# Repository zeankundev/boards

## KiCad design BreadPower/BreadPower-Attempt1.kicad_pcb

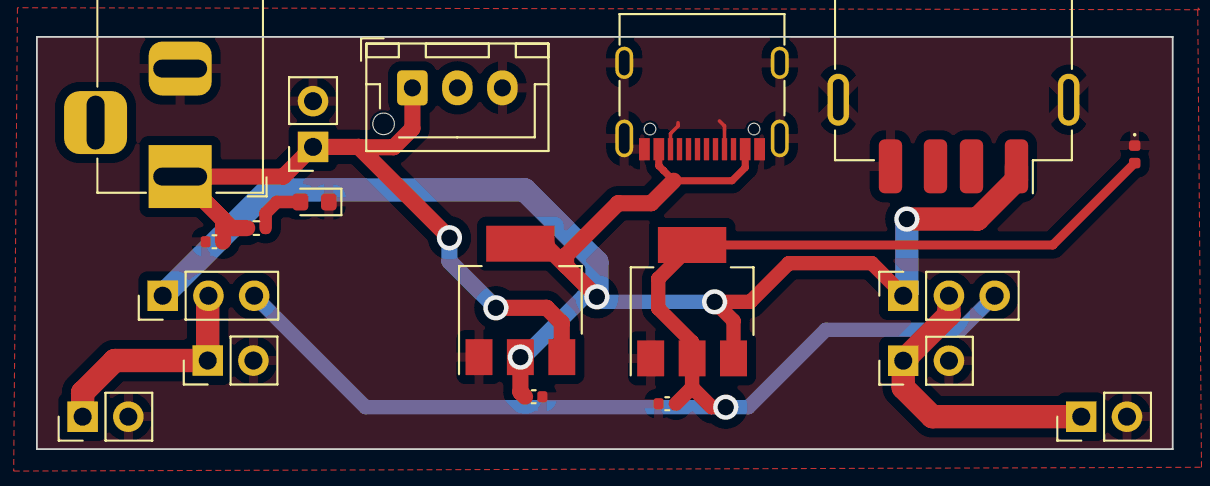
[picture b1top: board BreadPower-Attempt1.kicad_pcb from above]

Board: 2 copper layers, 63.1 x 22.9 mm, 19 parts (0 on the bottom side), 7 nets.

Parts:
C1: 22u; C_0402_1005Metric
C2: 8uF; C_0402_1005Metric
C3: 12uF; C_0402_1005Metric
D1: D; D_0603_1608Metric
D2: GREEN; LED_0402_1005Metric
J1: Barrel_Jack_MountingPin; BarrelJack_Horizontal
J2: USB_C_Receptacle_USB2.0; USB_C_Receptacle_G-Switch_GT-USB-7010ASV
J3: USB_A; USB_A_Receptacle_GCT_USB1046
J4: Conn_01x03_Socket; JST_XH_B3B-XH-AM_1x03_P2.50mm_Vertical
J5: Conn_01x03; PinHeader_1x03_P2.54mm_Vertical
J6: Conn_01x02; PinSocket_1x02_P2.54mm_Vertical
J7: Conn_01x03; PinSocket_1x03_P2.54mm_Vertical
J8, J9, J10, J11: Conn_01x02; PinHeader_1x02_P2.54mm_Vertical
R1: 3; R_0402_1005Metric
U1: AMS1117-5.0; SOT-223-3_TabPin2
U2: AMS1117-3.3; SOT-223-3_TabPin2

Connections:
+3.3V: C3.1, D2.2 (A), J5.3, J7.3, U2.2 (VO)
+5V: C2.1, J2.A4 (VBUS), J2.A9 (VBUS), J2.B4 (VBUS), J2.B9 (VBUS), J3.1 (VBUS), J5.1, J7.1, U1.2 (VO), U2.3 (VI)
/OUTPUT_VDD_1: J5.2, J8.1, J11.1
/OUTPUT_VDD_2: J7.2, J9.1, J10.1
GND: C1.2, C2.2, C3.2, D1.1 (K), D2.1 (K), J1.2, J2.A1 (GND), J2.A5 (CC1), J2.A12 (GND), J2.B1 (GND), J2.B5 (CC2), J2.B12 (GND), J2.S1 (SHIELD), J3.4 (GND), J3.5 (Shield), J4.3, J6.2, J8.2, J9.2, J10.2, J11.2, U1.1 (GND), U2.1 (GND)
unnamed: D1.2 (A), R1.2
VDD: C1.1, J1.1, J4.1, J6.1, R1.1, U1.3 (VI)

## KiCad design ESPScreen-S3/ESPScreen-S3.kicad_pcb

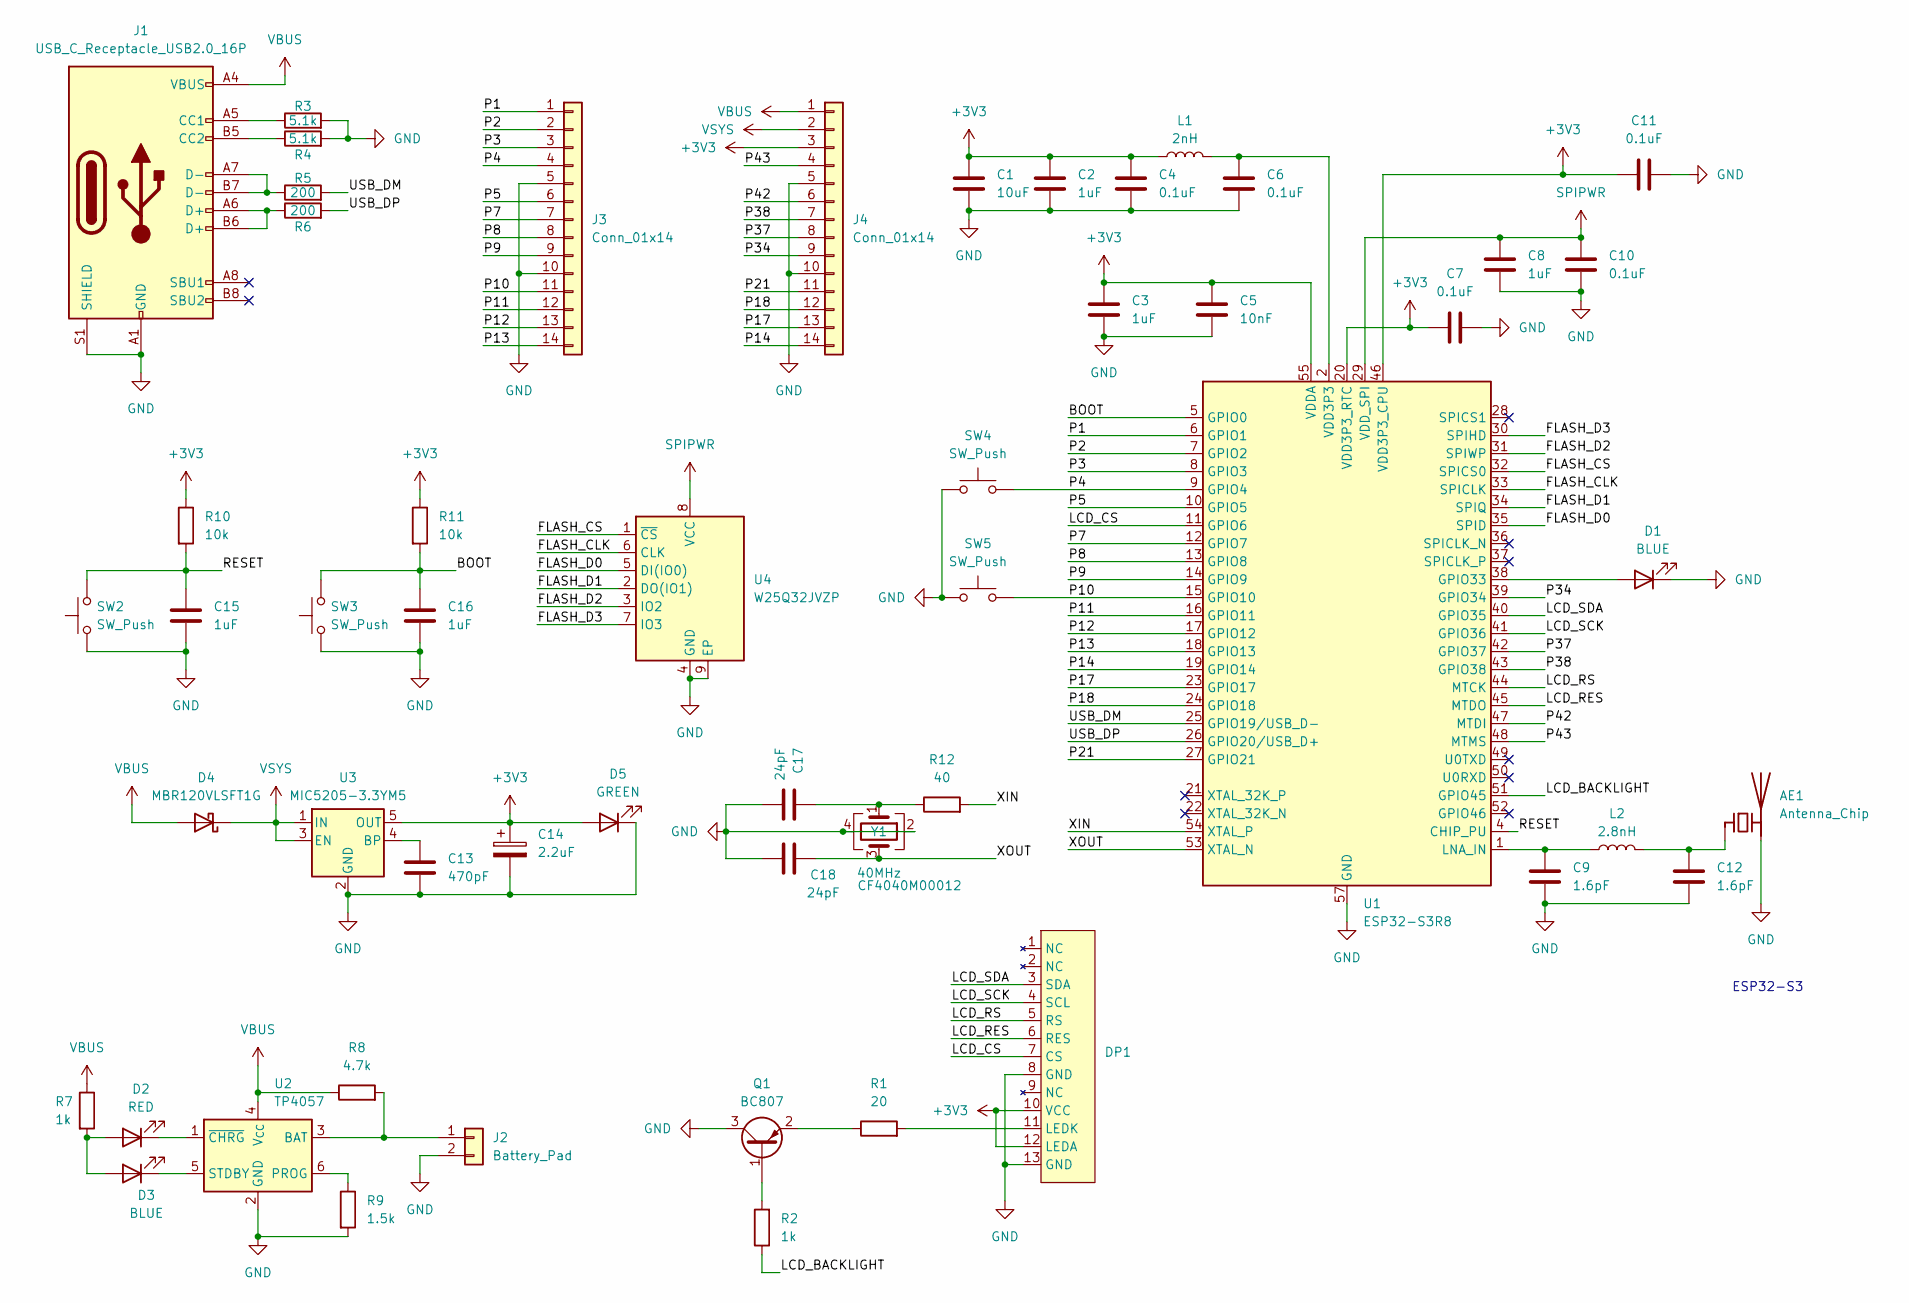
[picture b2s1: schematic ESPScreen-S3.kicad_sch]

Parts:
AE1: Antenna_Chip; Texas_SWRA117D_2.4GHz_Left
C1: 10uF; C_0402_1005Metric
C2, C3, C8, C15, C16: 1uF; C_0402_1005Metric
C4, C6, C7, C10, C11: 0.1uF; C_0402_1005Metric
C5: 10nF; C_0402_1005Metric
C9, C12: 1.6pF; C_0402_1005Metric
C13: 470pF; C_0402_1005Metric
C14: 2.2uF; CP_EIA-1608-08_AVX-J
C17, C18: 24pF; C_0402_1005Metric
D1, D3: BLUE; LED_0402_1005Metric
D2: RED; LED_0402_1005Metric
D4: MBR120VLSFT1G; D_SOD-123F
D5: GREEN; LED_0402_1005Metric
DP1: N114-2413THBIG01-H13
J1: USB_C_Receptacle_USB2.0_16P; USB_C_Receptacle_GCT_USB4105-xx-A_16P_TopMnt_Horizontal
J2: Battery_Pad; SolderWire-0.1sqmm_1x02_P3.6mm_D0.4mm_OD1mm
J3, J4: Conn_01x14; PinHeader_1x14_P2.54mm_Vertical
L1: 2nH; L_0402_1005Metric
L2: 2.8nH; L_0402_1005Metric
Q1: BC807; SOT-23
R1: 20; R_0402_1005Metric
R2, R7: 1k; R_0402_1005Metric
R3, R4: 5.1k; R_0402_1005Metric
R5, R6: 200; R_0402_1005Metric
R8: 4.7k; R_0402_1005Metric
R9: 1.5k; R_0402_1005Metric
R10, R11: 10k; R_0402_1005Metric
R12: 40; R_0402_1005Metric
SW2, SW3: SW_Push; SW_SPST_EVQP7C
SW4, SW5: SW_Push; SW_Push_1P1T_NO_Vertical_Wuerth_434133025816
U1: ESP32-S3R8; QFN-56-1EP_7x7mm_P0.4mm_EP4x4mm
U2: TP4057; TSOT-23-6
U3: MIC5205-3.3YM5; SOT-23-5
U4: W25Q32JVZP; WSON-8-1EP_6x5mm_P1.27mm_EP3.4x4.3mm
Y1: 40MHz; Crystal_SMD_3225-4Pin_3.2x2.5mm

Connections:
+3V3: C1.1, C2.1, C3.1, C4.1, C5.1, C7.1, C11.1, C14.1, D5.2 (A), DP1.10 (VCC), DP1.12 (LEDA), J4.3, L1.1, R10.1, R11.1, U1.20 (VDD3P3_RTC), U1.46 (VDD3P3_CPU), U1.55 (VDDA), U1.56 (VDDA), U3.5 (OUT)
/BOOT: C16.1, R11.2, SW3.2, U1.5 (GPIO0)
/FLASH_CLK: U1.33 (SPICLK), U4.6 (CLK)
/FLASH_CS: U1.32 (SPICS0), U4.1 (~CS)
/FLASH_D0: U1.35 (SPID), U4.5 (DI(IO0))
/FLASH_D1: U1.34 (SPIQ), U4.2 (DO(IO1))
/FLASH_D2: U1.31 (SPIWP), U4.3 (IO2)
/FLASH_D3: U1.30 (SPIHD), U4.7 (IO3)
/LCD_BACKLIGHT: R2.1, U1.51 (GPIO45)
/LCD_CS: DP1.7 (CS), U1.11 (GPIO6)
/LCD_RES: DP1.6 (RES), U1.45 (MTDO)
/LCD_RS: DP1.5 (RS), U1.44 (MTCK)
/LCD_SCK: DP1.4 (SCL), U1.41 (GPIO36)
/LCD_SDA: DP1.3 (SDA), U1.40 (GPIO35)
/P1: J3.1, U1.6 (GPIO1)
/P2: J3.2, U1.7 (GPIO2)
/P3: J3.3, U1.8 (GPIO3)
/P4: J3.4, SW4.2, U1.9 (GPIO4)
/P5: J3.6, U1.10 (GPIO5)
/P7: J3.7, U1.12 (GPIO7)
/P8: J3.8, U1.13 (GPIO8)
/P9: J3.9, U1.14 (GPIO9)
/P10: J3.11, SW5.2, U1.15 (GPIO10)
/P11: J3.12, U1.16 (GPIO11)
/P12: J3.13, U1.17 (GPIO12)
/P13: J3.14, U1.18 (GPIO13)
/P14: J4.14, U1.19 (GPIO14)
/P17: J4.13, U1.23 (GPIO17)
/P18: J4.12, U1.24 (GPIO18)
/P21: J4.11, U1.27 (GPIO21)
/P34: J4.9, U1.39 (GPIO34)
/P37: J4.8, U1.42 (GPIO37)
/P38: J4.7, U1.43 (GPIO38)
/P42: J4.6, U1.47 (MTDI)
/P43: J4.4, U1.48 (MTMS)
/RESET: C15.1, R10.2, SW2.2, U1.4 (CHIP_PU)
/USB_DM: R5.2, U1.25 (GPIO19/USB_D-)
/USB_DP: R6.2, U1.26 (GPIO20/USB_D+)
/XIN: R12.2, U1.54 (XTAL_P)
/XOUT: C18.1, U1.53 (XTAL_N), Y1.3
GND: AE1.2 (PCB_Trace), C1.2, C2.2, C3.2, C4.2, C5.2, C6.2, C7.2, C8.2, C9.2, C10.1, C11.2, C12.2, C13.2, C14.2, C15.2, C16.2, C17.2, C18.2, D1.1 (K), D5.1 (K), DP1.8 (GND), DP1.13 (GND), J1.A1 (GND), J1.A12 (GND), J1.B1 (GND), J1.B12 (GND), J1.S1 (SHIELD), J2.2, J3.5, J3.10, J4.5, J4.10, Q1.3 (C), R3.2, R4.2, R9.2, SW2.1, SW3.1, SW4.1, SW5.1, U1.57 (GND), U2.2 (GND), U3.2 (GND), U4.4 (GND), U4.9 (EP), Y1.2, Y1.4
unnamed: AE1.1 (FEED), C12.1, L2.2
unnamed: C6.1, L1.2, U1.2 (VDD3P3), U1.3 (VDD3P3)
unnamed: C17.1, R12.1, Y1.1
unnamed: D1.2 (A), U1.38 (GPIO33)
unnamed: D2.2 (A), D3.2 (A), R7.2
unnamed: D2.1 (K), U2.1 (~CHRG)
unnamed: D3.1 (K), U2.5 (STDBY)
unnamed: DP1.11 (LEDK), R1.2
unnamed: J1.A5 (CC1), R3.1
unnamed: J1.B5 (CC2), R4.1
unnamed: J1.A6 (D+), J1.B6 (D+), R6.1
unnamed: J1.A7 (D-), J1.B7 (D-), R5.1
unnamed: J2.1, R8.2, U2.3 (BAT)
unnamed: Q1.1 (B), R2.2
unnamed: Q1.2 (E), R1.1
unnamed: C9.1, L2.1, U1.1 (LNA_IN)
unnamed: R9.1, U2.6 (PROG)
unnamed: C13.1, U3.4 (BP)
SPIPWR: C8.1, C10.2, U1.29 (VDD_SPI), U4.8 (VCC)
VBUS: D4.2 (A), J1.A4 (VBUS), J1.A9 (VBUS), J1.B4 (VBUS), J1.B9 (VBUS), J4.1, R7.1, R8.1, U2.4 (V_{CC})
VSYS: D4.1 (K), J4.2, U3.1 (IN), U3.3 (EN)

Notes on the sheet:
ESP32-S3

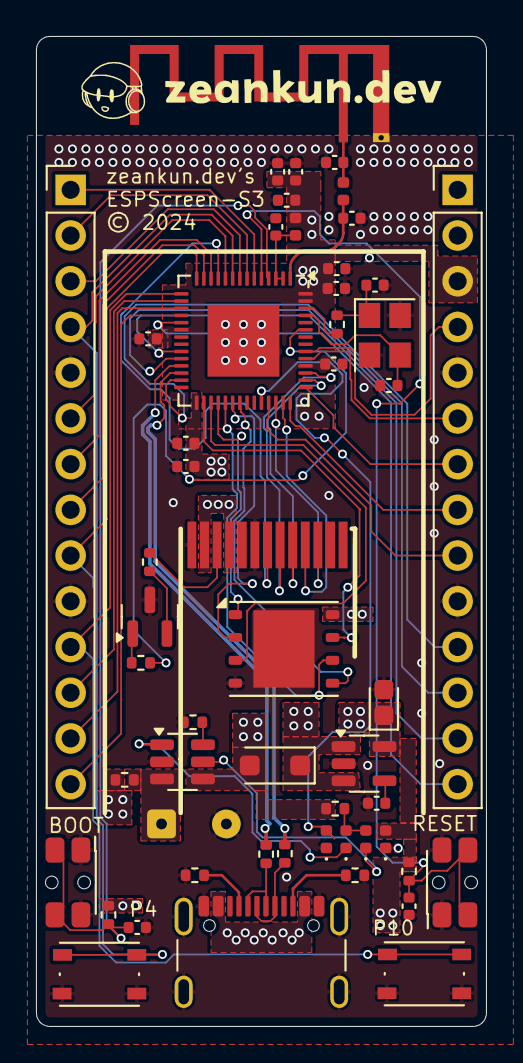
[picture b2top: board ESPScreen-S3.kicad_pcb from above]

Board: 4 copper layers, 25.0 x 55.0 mm, 53 parts (0 on the bottom side), 62 nets.

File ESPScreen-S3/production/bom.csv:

Designator,Footprint,Quantity,Value,LCSC Part #
AE1,Texas_SWRA117D_2.4GHz_Left,1,Antenna_Chip,
C1,0402,1,10uF,
"C10, C11, C4, C6, C7",0402,5,0.1uF,
"C12, C9",0402,2,1.6pF,
C13,0402,1,470pF,
C14,CP_EIA-1608-08_AVX-J,1,2.2uF,
"C15, C16, C2, C3, C8",0402,5,1uF,
"C17, C18",0402,2,24pF,
C5,0402,1,10nF,
"D1, D3",0402,2,BLUE,
D2,0402,1,RED,
D4,D_SOD-123F,1,MBR120VLSFT1G,
D5,0402,1,GREEN,
DP1,N114-2413THBIG01-H13,1,~,
J1,USB_C_Receptacle_GCT_USB4105-xx-A_16P_TopMnt_Horizontal,1,USB_C_Receptacle_USB2.0_16P,
J2,SolderWire-0.1sqmm_1x02_P3.6mm_D0.4mm_OD1mm,1,Battery_Pad,
"J3, J4",PinHeader_1x14_P2.54mm_Vertical,2,Conn_01x14,
L1,0402,1,2nH,
L2,0402,1,2.8nH,
Q1,SOT-23,1,BC807,
R1,0402,1,20,
"R10, R11",0402,2,10k,
R12,0402,1,40,
"R2, R7",0402,2,1k,
"R3, R4",0402,2,5.1k,
"R5, R6",0402,2,200,
R8,0402,1,4.7k,
R9,0402,1,1.5k,
"SW2, SW3",SW_SPST_EVQP7C,2,SW_Push,
"SW4, SW5",SW_Push_1P1T_NO_Vertical_Wuerth_434133025816,2,SW_Push,
U1,QFN-56-1EP_7x7mm_P0.4mm_EP4x4mm,1,ESP32-S3R8,
U2,TSOT-23-6,1,TP4057,
U3,SOT-23-5,1,MIC5205-3.3YM5,
U4,WSON-8-1EP_6x5mm_P1.27mm_EP3.4x4.3mm,1,W25Q32JVZP,
Y1,Crystal_SMD_3225-4Pin_3.2x2.5mm,1,40MHz,

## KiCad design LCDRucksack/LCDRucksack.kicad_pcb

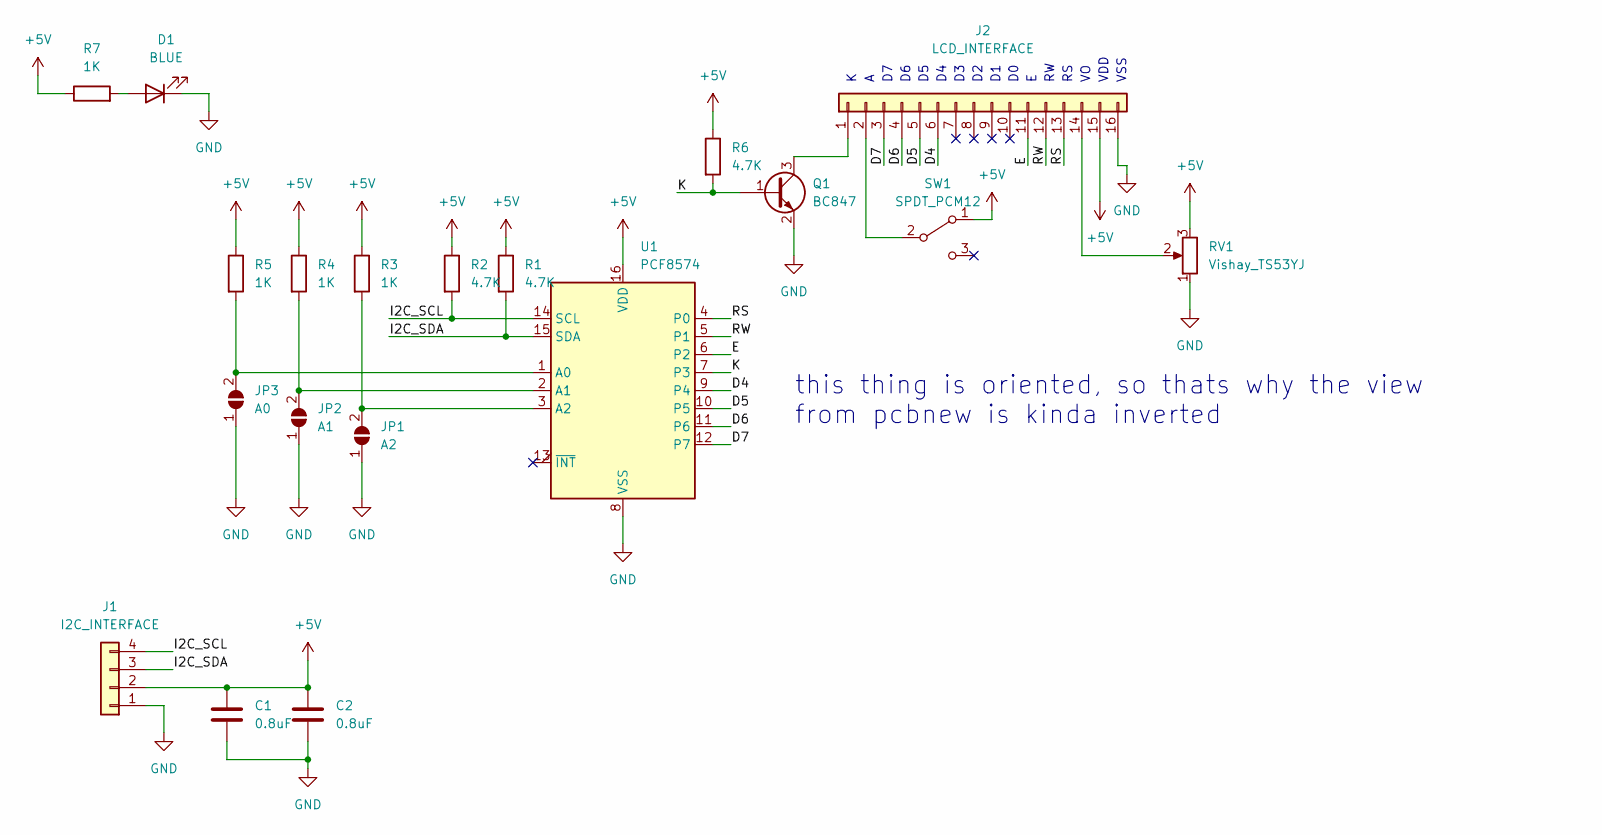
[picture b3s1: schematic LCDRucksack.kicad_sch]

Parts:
C1, C2: 0.8uF; C_0402_1005Metric
D1: BLUE; LED_0402_1005Metric
J1: I2C_INTERFACE; Conn_01x04_2.54mm
J2: LCD_INTERFACE; Conn_01x16_2.54mm
JP1: A2; SolderJumper-2_P1.3mm_Open_TrianglePad1.0x1.5mm
JP2: A1; SolderJumper-2_P1.3mm_Open_TrianglePad1.0x1.5mm
JP3: A0; SolderJumper-2_P1.3mm_Open_TrianglePad1.0x1.5mm
Q1: BC847; SOT-23
R1, R2, R6: 4.7K; R_0402_1005Metric
R3, R4, R5, R7: 1K; R_0402_1005Metric
RV1: Vishay_TS53YJ; Potentiometer_Vishay_TS53YJ_Vertical
SW1: SPDT_PCM12; SW_SPDT_PCM12
U1: PCF8574; SOIC-16W_7.5x10.3mm_P1.27mm

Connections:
+5V: C1.1, C2.1, J1.2, J2.15, R1.1, R2.1, R3.1, R4.1, R5.1, R6.1, R7.1, RV1.3, SW1.1 (A), U1.16 (VDD)
/D4: J2.6, U1.9 (P4)
/D5: J2.5, U1.10 (P5)
/D6: J2.4, U1.11 (P6)
/D7: J2.3, U1.12 (P7)
/E: J2.11, U1.6 (P2)
/I2C_SCL: J1.4, R2.2, U1.14 (SCL)
/I2C_SDA: J1.3, R1.2, U1.15 (SDA)
/K: Q1.1 (B), R6.2, U1.7 (P3)
/RS: J2.13, U1.4 (P0)
/RW: J2.12, U1.5 (P1)
GND: C1.2, C2.2, D1.1 (K), J1.1, J2.16, JP1.1 (A), JP2.1 (A), JP3.1 (A), Q1.2 (E), RV1.1, U1.8 (VSS)
unnamed: D1.2 (A), R7.2
unnamed: J2.1, Q1.3 (C)
unnamed: J2.2, SW1.2 (B)
unnamed: J2.14, RV1.2
unnamed: JP1.2 (B), R3.2, U1.3 (A2)
unnamed: JP2.2 (B), R4.2, U1.2 (A1)
unnamed: JP3.2 (B), R5.2, U1.1 (A0)

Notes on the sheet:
this thing is oriented, so thats why the view from pcbnew is kinda inverted
VDD
VSS

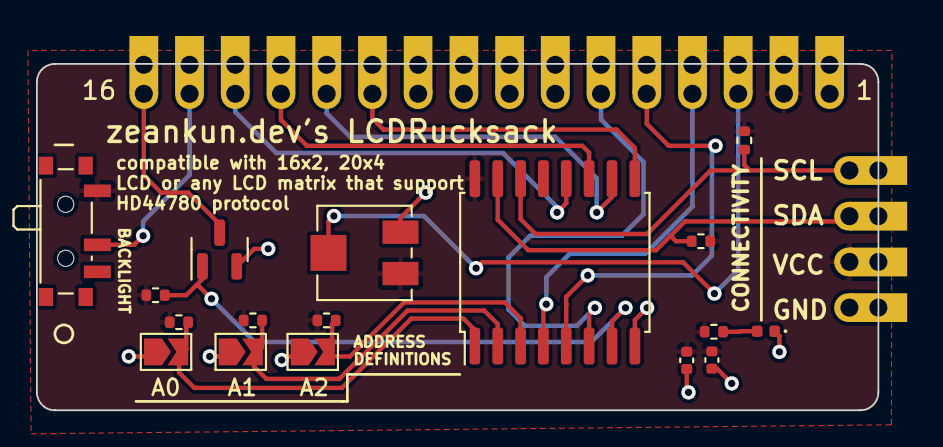
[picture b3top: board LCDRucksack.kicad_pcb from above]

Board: 2 copper layers, 46.8 x 19.2 mm, 19 parts (1 on the bottom side), 19 nets.

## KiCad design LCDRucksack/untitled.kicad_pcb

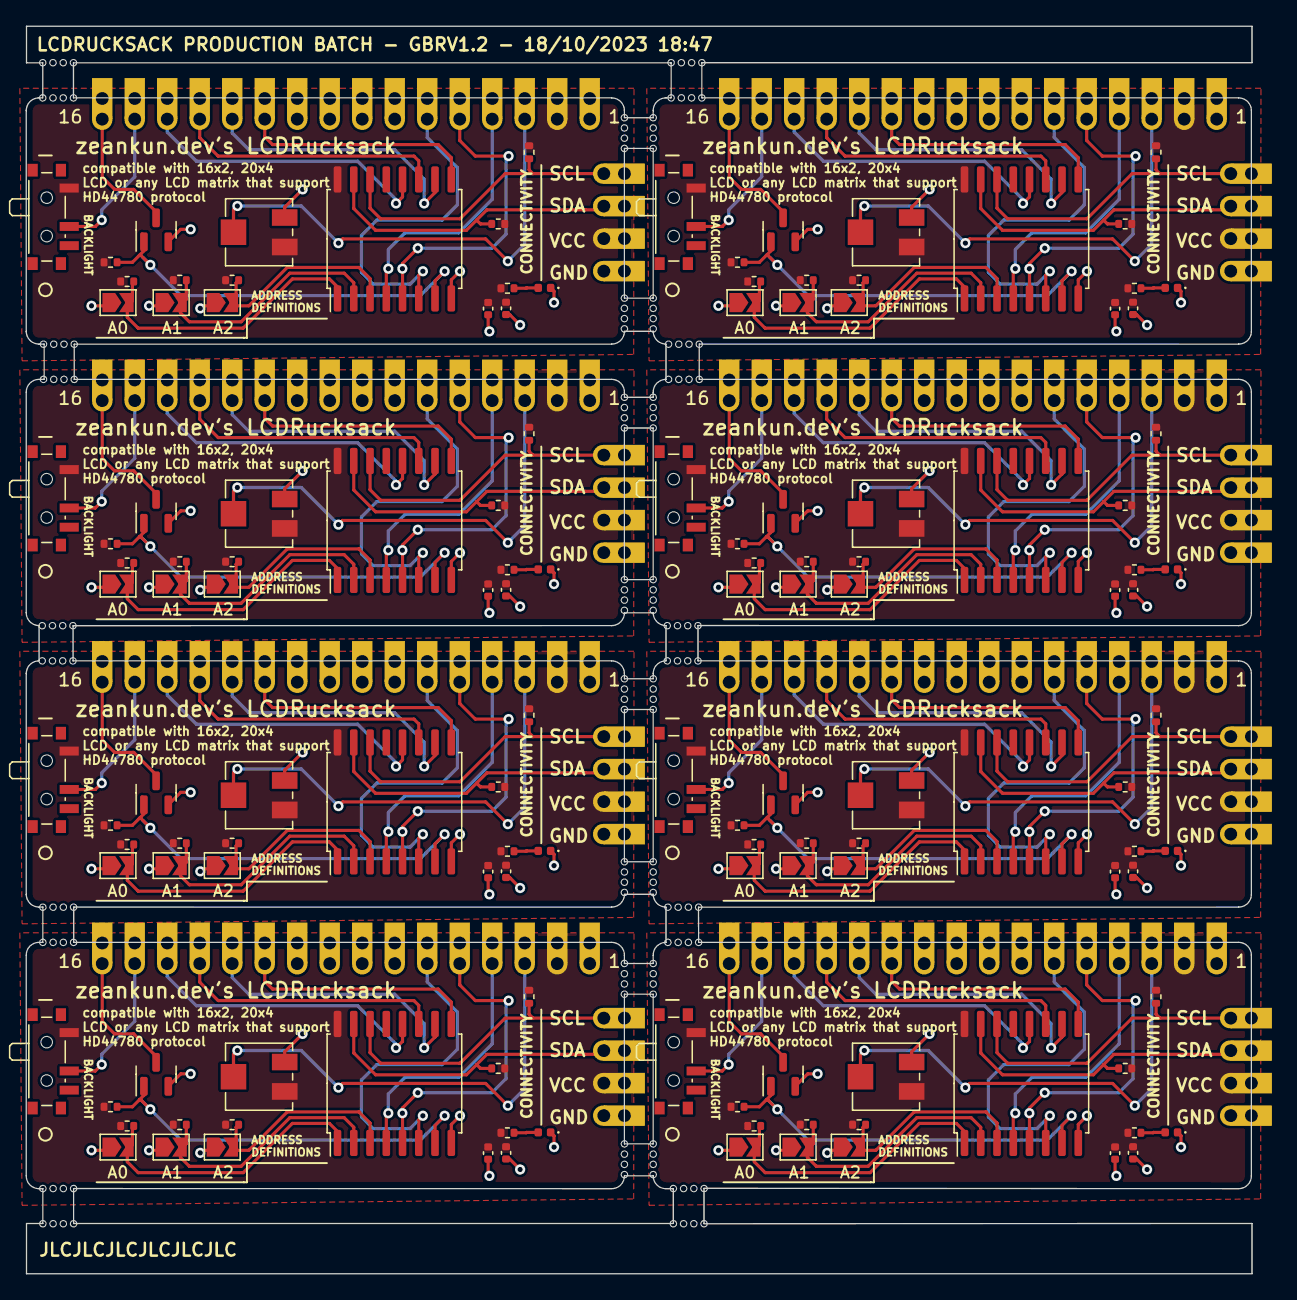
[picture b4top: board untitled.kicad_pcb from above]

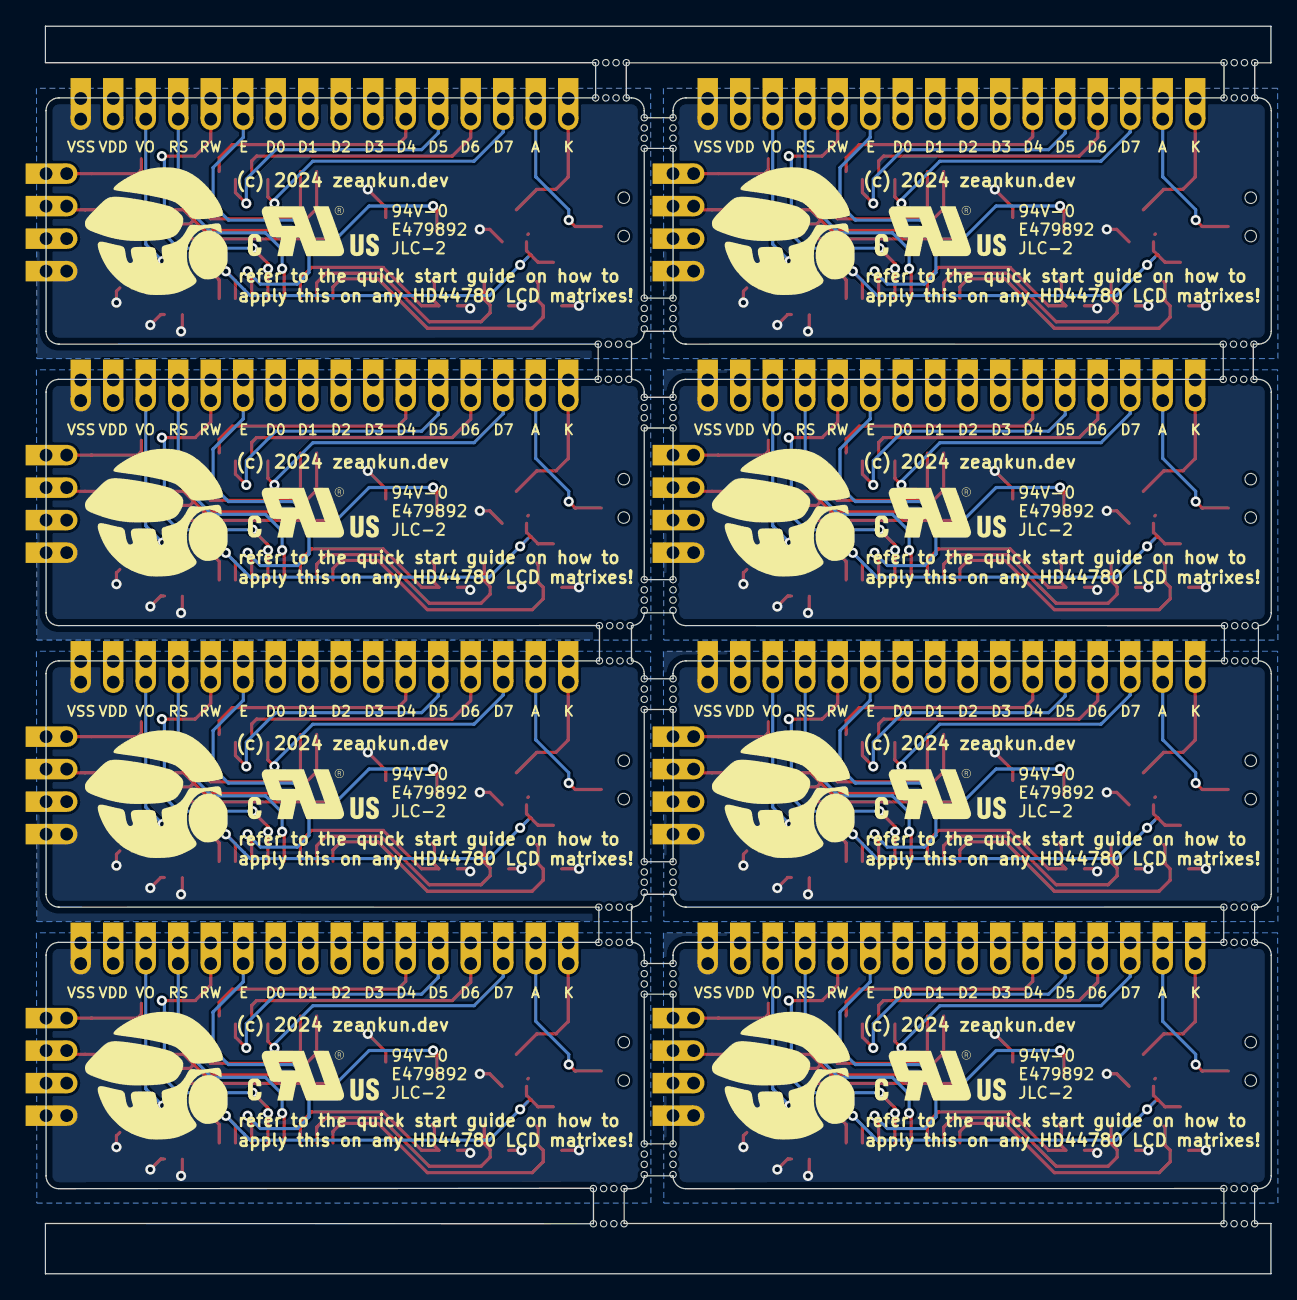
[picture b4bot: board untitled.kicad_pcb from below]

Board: 2 copper layers, 95.8 x 97.5 mm, 152 parts (8 on the bottom side), 19 nets.

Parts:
C1, C2, C3, C4, C5, C6, C7, C8, C9, C10, C11, C12, C13, C14, C15, C16: 0.8uF; C_0402_1005Metric
D1, D2, D3, D4, D5, D6, D7, D8: BLUE; LED_0402_1005Metric
J1, J3, J5, J7, J9, J11, J13, J15: I2C_INTERFACE; Conn_01x04_2.54mm
J2, J4, J6, J8, J10, J12, J14, J16: LCD_INTERFACE; Conn_01x16_2.54mm
JP1, JP4, JP7, JP10, JP13, JP16, JP19, JP22: A2; SolderJumper-2_P1.3mm_Open_TrianglePad1.0x1.5mm
JP2, JP5, JP8, JP11, JP14, JP17, JP20, JP23: A1; SolderJumper-2_P1.3mm_Open_TrianglePad1.0x1.5mm
JP3, JP6, JP9, JP12, JP15, JP18, JP21, JP24: A0; SolderJumper-2_P1.3mm_Open_TrianglePad1.0x1.5mm
Q1, Q2, Q3, Q4, Q5, Q6, Q7, Q8: BC847; SOT-23
R1, R2, R6, R8, R9, R13, R15, R16, R20, R22, R23, R27, R29, R30, R34, R36, R37, R41, R43, R44, R48, R50, R51, R55: 4.7K; R_0402_1005Metric
R3, R4, R5, R7, R10, R11, R12, R14, R17, R18, R19, R21, R24, R25, R26, R28, R31, R32, R33, R35, R38, R39, R40, R42, R45, R46, R47, R49, R52, R53, R54, R56: 1K; R_0402_1005Metric
RV1, RV2, RV3, RV4, RV5, RV6, RV7, RV8: Vishay_TS53YJ; Potentiometer_Vishay_TS53YJ_Vertical
SW1, SW2, SW3, SW4, SW5, SW6, SW7, SW8: SPDT_PCM12; SW_SPDT_PCM12
U1, U2, U3, U4, U5, U6, U7, U8: PCF8574; SOIC-16W_7.5x10.3mm_P1.27mm

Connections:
+5V: C1.1, C2.1, C3.1, C4.1, C5.1, C6.1, C7.1, C8.1, C9.1, C10.1, C11.1, C12.1, C13.1, C14.1, C15.1, C16.1, J1.2, J2.15, J3.2, J4.15, J5.2, J6.15, J7.2, J8.15, J9.2, J10.15, J11.2, J12.15, J13.2, J14.15, J15.2, J16.15, R1.1, R2.1, R3.1, R4.1, R5.1, R6.1, R7.1, R8.1, R9.1, R10.1, R11.1, R12.1, R13.1, R14.1, R15.1, R16.1, R17.1, R18.1, R19.1, R20.1, R21.1, R22.1, R23.1, R24.1, R25.1, R26.1, R27.1, R28.1, R29.1, R30.1, R31.1, R32.1, R33.1, R34.1, R35.1, R36.1, R37.1, R38.1, R39.1, R40.1, R41.1, R42.1, R43.1, R44.1, R45.1, R46.1, R47.1, R48.1, R49.1, R50.1, R51.1, R52.1, R53.1, R54.1, R55.1, R56.1, RV1.3, RV2.3, RV3.3, RV4.3, RV5.3, RV6.3, RV7.3, RV8.3, SW1.1 (A), SW2.1 (A), SW3.1 (A), SW4.1 (A), SW5.1 (A), SW6.1 (A), SW7.1 (A), SW8.1 (A), U1.16 (VDD), U2.16 (VDD), U3.16 (VDD), U4.16 (VDD), U5.16 (VDD), U6.16 (VDD), U7.16 (VDD), U8.16 (VDD)
/D4: J2.6, J4.6, J6.6, J8.6, J10.6, J12.6, J14.6, J16.6, U1.9 (P4), U2.9 (P4), U3.9 (P4), U4.9 (P4), U5.9 (P4), U6.9 (P4), U7.9 (P4), U8.9 (P4)
/D5: J2.5, J4.5, J6.5, J8.5, J10.5, J12.5, J14.5, J16.5, U1.10 (P5), U2.10 (P5), U3.10 (P5), U4.10 (P5), U5.10 (P5), U6.10 (P5), U7.10 (P5), U8.10 (P5)
/D6: J2.4, J4.4, J6.4, J8.4, J10.4, J12.4, J14.4, J16.4, U1.11 (P6), U2.11 (P6), U3.11 (P6), U4.11 (P6), U5.11 (P6), U6.11 (P6), U7.11 (P6), U8.11 (P6)
/D7: J2.3, J4.3, J6.3, J8.3, J10.3, J12.3, J14.3, J16.3, U1.12 (P7), U2.12 (P7), U3.12 (P7), U4.12 (P7), U5.12 (P7), U6.12 (P7), U7.12 (P7), U8.12 (P7)
/E: J2.11, J4.11, J6.11, J8.11, J10.11, J12.11, J14.11, J16.11, U1.6 (P2), U2.6 (P2), U3.6 (P2), U4.6 (P2), U5.6 (P2), U6.6 (P2), U7.6 (P2), U8.6 (P2)
/I2C_SCL: J1.4, J3.4, J5.4, J7.4, J9.4, J11.4, J13.4, J15.4, R2.2, R9.2, R16.2, R23.2, R30.2, R37.2, R44.2, R51.2, U1.14 (SCL), U2.14 (SCL), U3.14 (SCL), U4.14 (SCL), U5.14 (SCL), U6.14 (SCL), U7.14 (SCL), U8.14 (SCL)
/I2C_SDA: J1.3, J3.3, J5.3, J7.3, J9.3, J11.3, J13.3, J15.3, R1.2, R8.2, R15.2, R22.2, R29.2, R36.2, R43.2, R50.2, U1.15 (SDA), U2.15 (SDA), U3.15 (SDA), U4.15 (SDA), U5.15 (SDA), U6.15 (SDA), U7.15 (SDA), U8.15 (SDA)
/K: Q1.1 (B), Q2.1 (B), Q3.1 (B), Q4.1 (B), Q5.1 (B), Q6.1 (B), Q7.1 (B), Q8.1 (B), R6.2, R13.2, R20.2, R27.2, R34.2, R41.2, R48.2, R55.2, U1.7 (P3), U2.7 (P3), U3.7 (P3), U4.7 (P3), U5.7 (P3), U6.7 (P3), U7.7 (P3), U8.7 (P3)
/RS: J2.13, J4.13, J6.13, J8.13, J10.13, J12.13, J14.13, J16.13, U1.4 (P0), U2.4 (P0), U3.4 (P0), U4.4 (P0), U5.4 (P0), U6.4 (P0), U7.4 (P0), U8.4 (P0)
/RW: J2.12, J4.12, J6.12, J8.12, J10.12, J12.12, J14.12, J16.12, U1.5 (P1), U2.5 (P1), U3.5 (P1), U4.5 (P1), U5.5 (P1), U6.5 (P1), U7.5 (P1), U8.5 (P1)
GND: C1.2, C2.2, C3.2, C4.2, C5.2, C6.2, C7.2, C8.2, C9.2, C10.2, C11.2, C12.2, C13.2, C14.2, C15.2, C16.2, D1.1 (K), D2.1 (K), D3.1 (K), D4.1 (K), D5.1 (K), D6.1 (K), D7.1 (K), D8.1 (K), J1.1, J2.16, J3.1, J4.16, J5.1, J6.16, J7.1, J8.16, J9.1, J10.16, J11.1, J12.16, J13.1, J14.16, J15.1, J16.16, JP1.1 (A), JP2.1 (A), JP3.1 (A), JP4.1 (A), JP5.1 (A), JP6.1 (A), JP7.1 (A), JP8.1 (A), JP9.1 (A), JP10.1 (A), JP11.1 (A), JP12.1 (A), JP13.1 (A), JP14.1 (A), JP15.1 (A), JP16.1 (A), JP17.1 (A), JP18.1 (A), JP19.1 (A), JP20.1 (A), JP21.1 (A), JP22.1 (A), JP23.1 (A), JP24.1 (A), Q1.2 (E), Q2.2 (E), Q3.2 (E), Q4.2 (E), Q5.2 (E), Q6.2 (E), Q7.2 (E), Q8.2 (E), RV1.1, RV2.1, RV3.1, RV4.1, RV5.1, RV6.1, RV7.1, RV8.1, U1.8 (VSS), U2.8 (VSS), U3.8 (VSS), U4.8 (VSS), U5.8 (VSS), U6.8 (VSS), U7.8 (VSS), U8.8 (VSS)
unnamed: D1.2 (A), D2.2 (A), D3.2 (A), D4.2 (A), D5.2 (A), D6.2 (A), D7.2 (A), D8.2 (A), R7.2, R14.2, R21.2, R28.2, R35.2, R42.2, R49.2, R56.2
unnamed: J2.1, J4.1, J6.1, J8.1, J10.1, J12.1, J14.1, J16.1, Q1.3 (C), Q2.3 (C), Q3.3 (C), Q4.3 (C), Q5.3 (C), Q6.3 (C), Q7.3 (C), Q8.3 (C)
unnamed: J2.2, J4.2, J6.2, J8.2, J10.2, J12.2, J14.2, J16.2, SW1.2 (B), SW2.2 (B), SW3.2 (B), SW4.2 (B), SW5.2 (B), SW6.2 (B), SW7.2 (B), SW8.2 (B)
unnamed: J2.14, J4.14, J6.14, J8.14, J10.14, J12.14, J14.14, J16.14, RV1.2, RV2.2, RV3.2, RV4.2, RV5.2, RV6.2, RV7.2, RV8.2
unnamed: JP1.2 (B), JP4.2 (B), JP7.2 (B), JP10.2 (B), JP13.2 (B), JP16.2 (B), JP19.2 (B), JP22.2 (B), R3.2, R10.2, R17.2, R24.2, R31.2, R38.2, R45.2, R52.2, U1.3 (A2), U2.3 (A2), U3.3 (A2), U4.3 (A2), U5.3 (A2), U6.3 (A2), U7.3 (A2), U8.3 (A2)
unnamed: JP2.2 (B), JP5.2 (B), JP8.2 (B), JP11.2 (B), JP14.2 (B), JP17.2 (B), JP20.2 (B), JP23.2 (B), R4.2, R11.2, R18.2, R25.2, R32.2, R39.2, R46.2, R53.2, U1.2 (A1), U2.2 (A1), U3.2 (A1), U4.2 (A1), U5.2 (A1), U6.2 (A1), U7.2 (A1), U8.2 (A1)
unnamed: JP3.2 (B), JP6.2 (B), JP9.2 (B), JP12.2 (B), JP15.2 (B), JP18.2 (B), JP21.2 (B), JP24.2 (B), R5.2, R12.2, R19.2, R26.2, R33.2, R40.2, R47.2, R54.2, U1.1 (A0), U2.1 (A0), U3.1 (A0), U4.1 (A0), U5.1 (A0), U6.1 (A0), U7.1 (A0), U8.1 (A0)

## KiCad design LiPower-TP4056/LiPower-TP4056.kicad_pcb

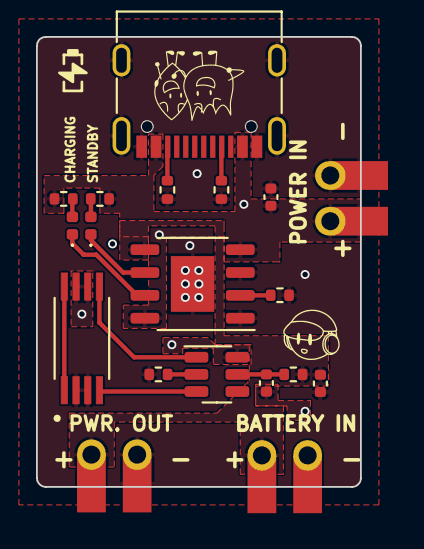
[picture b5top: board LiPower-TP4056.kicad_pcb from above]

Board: 2 copper layers, 18.0 x 25.0 mm, 19 parts (0 on the bottom side), 15 nets.

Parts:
C1, C2: 100n; C_0402_1005Metric
C3: 10u; C_0402_1005Metric
D1: RED; LED_0402_1005Metric
D2: GREEN; LED_0402_1005Metric
J1: USB_C_Receptacle_USB2.0; USB_C_Receptacle_G-Switch_GT-USB-7010ASV
J2, J3, J4: Conn_01x02; Conn_01x02_2.54mm
Q1: FS8205A; SOP65P640X120-8N
R1, R2: 5.1k; R_0402_1005Metric
R3: 1.2k; R_0402_1005Metric
R4, R5, R6: 1k; R_0402_1005Metric
R7: 100; R_0402_1005Metric
U1: TP4056; HSOP-8-1EP_3.9x4.9mm_P1.27mm_EP2.41x3.1mm
U2: DW01A; SOT-23-6

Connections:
+BATT: C3.1, J3.1, J4.1, R7.2, U1.5 (BAT)
-BATT: C2.2, J3.2, Q1.6, Q1.7, U2.6 (VSS)
GND: C1.2, C3.2, J1.A1 (GND), J1.A12 (GND), J1.B1 (GND), J1.B12 (GND), J1.S1 (SHIELD), J2.2, J4.2, Q1.2, Q1.3, R1.2, R2.2, R3.2, R6.2, U1.1 (TEMP), U1.3 (GND), U1.9 (EP)
unnamed: D1.2 (A), R4.2
unnamed: D1.1 (K), U1.7 (CHRG)
unnamed: D2.2 (A), R5.2
unnamed: D2.1 (K), U1.6 (STDBY)
unnamed: J1.A5 (CC1), R1.1
unnamed: J1.B5 (CC2), R2.1
unnamed: R3.1, U1.2 (PROG)
unnamed: Q1.4, U2.3 (COUT)
unnamed: R6.1, U2.2 (CS)
unnamed: Q1.5, U2.1 (DOUT)
unnamed: C2.1, R7.1, U2.5 (VDD)
VBUS: C1.1, J1.A4 (VBUS), J1.A9 (VBUS), J1.B4 (VBUS), J1.B9 (VBUS), J2.1, R4.1, R5.1, U1.4 (VCC), U1.8 (CE)

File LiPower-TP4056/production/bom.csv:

Designator,Footprint,Quantity,Value,LCSC Part #
"C1, C2",0402,2,100n,
C3,0402,1,10u,
D1,0402,1,RED,
D2,0402,1,GREEN,
J1,USB_C_Receptacle_G-Switch_GT-USB-7010ASV,1,USB_C_Receptacle_USB2.0,
Q1,SOP65P640X120-8N,1,FS8205A,
"R1, R2",0402,2,5.1k,
R3,0402,1,1.2k,
"R4, R5, R6",0402,3,1k,
R7,0402,1,100,
U1,HSOP-8-1EP_3.9x4.9mm_P1.27mm_EP2.41x3.1mm,1,TP4056,
U2,SOT-23-6,1,DW01A,

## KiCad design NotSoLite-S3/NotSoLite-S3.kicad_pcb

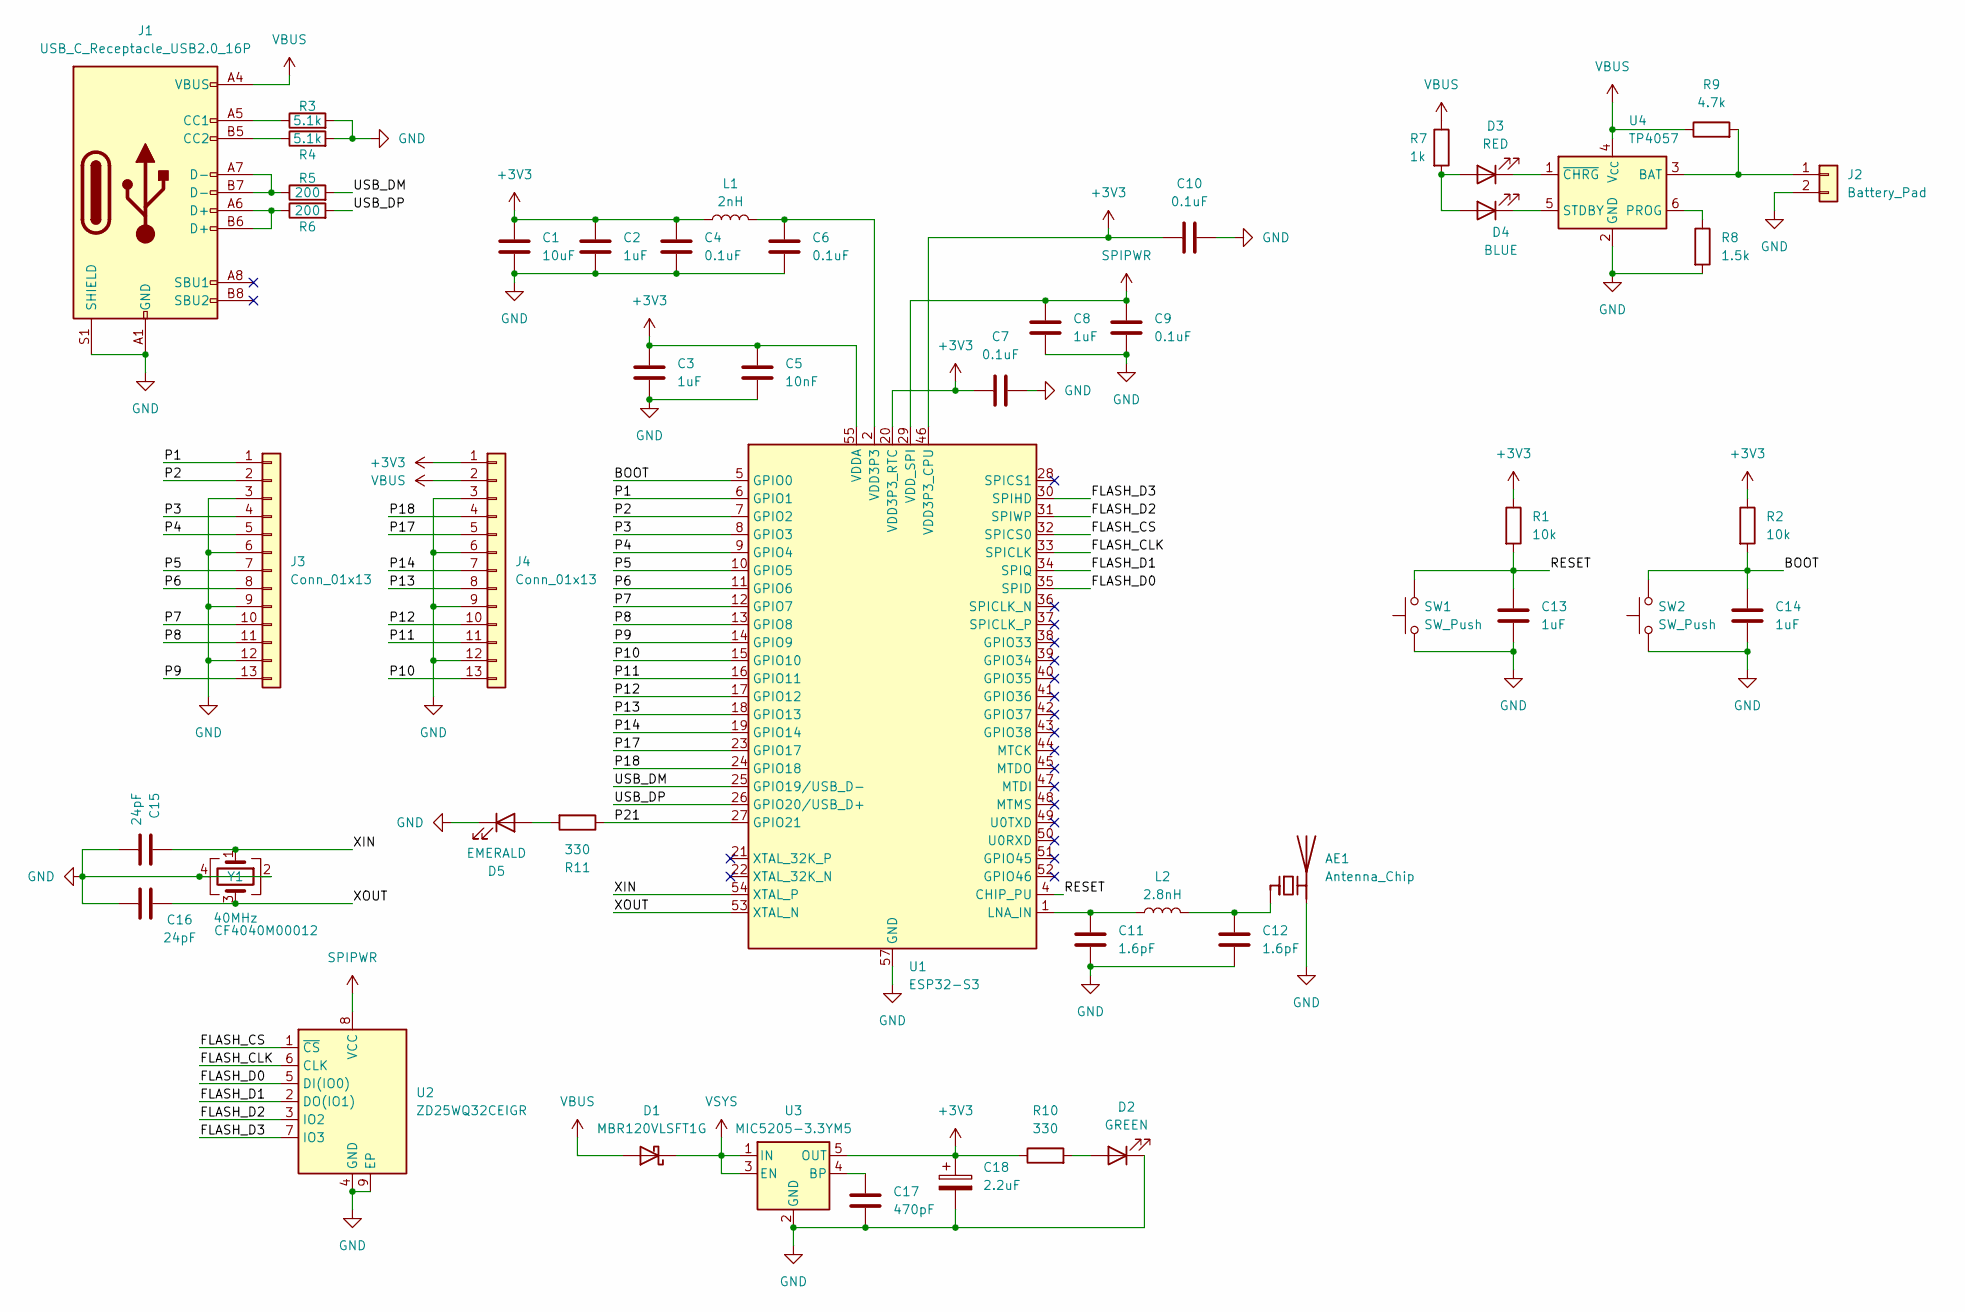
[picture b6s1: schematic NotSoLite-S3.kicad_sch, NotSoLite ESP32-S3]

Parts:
AE1: Antenna_Chip; Texas_SWRA117D_2.4GHz_Left
C1: 10uF; C_0402_1005Metric
C2, C3, C8, C13, C14: 1uF; C_0402_1005Metric
C4, C6, C7, C9, C10: 0.1uF; C_0402_1005Metric
C5: 10nF; C_0402_1005Metric
C11, C12: 1.6pF; C_0402_1005Metric
C15, C16: 24pF; C_0402_1005Metric
C17: 470pF; C_0402_1005Metric
C18: 2.2uF; CP_EIA-1608-08_AVX-J
D1: MBR120VLSFT1G; D_SOD-123F
D2: GREEN; LED_0402_1005Metric
D3: RED; LED_0402_1005Metric
D4: BLUE; LED_0402_1005Metric
D5: EMERALD; LED_0402_1005Metric
J1: USB_C_Receptacle_USB2.0_16P; USB_C_Receptacle_GCT_USB4105-xx-A_16P_TopMnt_Horizontal
J2: Battery_Pad; JST_GH_SM02B-GHS-TB_1x02-1MP_P1.25mm_Horizontal
J3, J4: Conn_01x13; 01x13_CHole
L1: 2nH; L_0402_1005Metric
L2: 2.8nH; L_0402_1005Metric
R1, R2: 10k; R_0402_1005Metric
R3, R4: 5.1k; R_0402_1005Metric
R5, R6: 200; R_0402_1005Metric
R7: 1k; R_0402_1005Metric
R8: 1.5k; R_0402_1005Metric
R9: 4.7k; R_0402_1005Metric
R10, R11: 330; R_0402_1005Metric
SW1, SW2: SW_Push; SW_Push_1P1T_NO_Vertical_Wuerth_434133025816
U1: ESP32-S3; QFN-56-1EP_7x7mm_P0.4mm_EP4x4mm
U2: ZD25WQ32CEIGR; Winbond_USON-8-1EP_3x2mm_P0.5mm_EP0.2x1.6mm
U3: MIC5205-3.3YM5; SOT-23-5
U4: TP4057; TSOT-23-6
Y1: 40MHz; Crystal_SMD_3225-4Pin_3.2x2.5mm

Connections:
+3V3: C1.1, C2.1, C3.1, C4.1, C5.1, C7.1, C10.1, C18.1, J4.1, L1.1, R1.1, R2.1, R10.1, U1.20 (VDD3P3_RTC), U1.46 (VDD3P3_CPU), U1.55 (VDDA), U1.56 (VDDA), U3.5 (OUT)
/BOOT: C14.1, R2.2, SW2.2, U1.5 (GPIO0)
/FLASH_CLK: U1.33 (SPICLK), U2.6 (CLK)
/FLASH_CS: U1.32 (SPICS0), U2.1 (~CS)
/FLASH_D0: U1.35 (SPID), U2.5 (DI(IO0))
/FLASH_D1: U1.34 (SPIQ), U2.2 (DO(IO1))
/FLASH_D2: U1.31 (SPIWP), U2.3 (IO2)
/FLASH_D3: U1.30 (SPIHD), U2.7 (IO3)
/P1: J3.1, U1.6 (GPIO1)
/P2: J3.2, U1.7 (GPIO2)
/P3: J3.4, U1.8 (GPIO3)
/P4: J3.5, U1.9 (GPIO4)
/P5: J3.7, U1.10 (GPIO5)
/P6: J3.8, U1.11 (GPIO6)
/P7: J3.10, U1.12 (GPIO7)
/P8: J3.11, U1.13 (GPIO8)
/P9: J3.13, U1.14 (GPIO9)
/P10: J4.13, U1.15 (GPIO10)
/P11: J4.11, U1.16 (GPIO11)
/P12: J4.10, U1.17 (GPIO12)
/P13: J4.8, U1.18 (GPIO13)
/P14: J4.7, U1.19 (GPIO14)
/P17: J4.5, U1.23 (GPIO17)
/P18: J4.4, U1.24 (GPIO18)
/P21: R11.1, U1.27 (GPIO21)
/RESET: C13.1, R1.2, SW1.2, U1.4 (CHIP_PU)
/USB_DM: R5.2, U1.25 (GPIO19/USB_D-)
/USB_DP: R6.2, U1.26 (GPIO20/USB_D+)
/XIN: C15.1, U1.54 (XTAL_P), Y1.1
/XOUT: C16.1, U1.53 (XTAL_N), Y1.3
GND: AE1.2 (PCB_Trace), C1.2, C2.2, C3.2, C4.2, C5.2, C6.2, C7.2, C8.2, C9.1, C10.2, C11.2, C12.2, C13.2, C14.2, C15.2, C16.2, C17.2, C18.2, D2.1 (K), D5.1 (K), J1.A1 (GND), J1.A12 (GND), J1.B1 (GND), J1.B12 (GND), J1.S1 (SHIELD), J2.2, J3.3, J3.6, J3.9, J3.12, J4.3, J4.6, J4.9, J4.12, R3.2, R4.2, R8.2, SW1.1, SW2.1, U1.57 (GND), U2.4 (GND), U2.9 (EP), U3.2 (GND), U4.2 (GND), Y1.2, Y1.4
unnamed: AE1.1 (FEED), C12.1, L2.2
unnamed: C6.1, L1.2, U1.2 (VDD3P3), U1.3 (VDD3P3)
unnamed: D2.2 (A), R10.2
unnamed: D3.2 (A), D4.2 (A), R7.2
unnamed: D3.1 (K), U4.1 (~CHRG)
unnamed: D4.1 (K), U4.5 (STDBY)
unnamed: D5.2 (A), R11.2
unnamed: J1.A5 (CC1), R3.1
unnamed: J1.B5 (CC2), R4.1
unnamed: J1.A6 (D+), J1.B6 (D+), R6.1
unnamed: J1.A7 (D-), J1.B7 (D-), R5.1
unnamed: J2.1, R9.2, U4.3 (BAT)
unnamed: C11.1, L2.1, U1.1 (LNA_IN)
unnamed: C17.1, U3.4 (BP)
unnamed: R8.1, U4.6 (PROG)
SPIPWR: C8.1, C9.2, U1.29 (VDD_SPI), U2.8 (VCC)
VBUS: D1.2 (A), J1.A4 (VBUS), J1.A9 (VBUS), J1.B4 (VBUS), J1.B9 (VBUS), J4.2, R7.1, R9.1, U4.4 (V_{CC})
VSYS: D1.1 (K), U3.1 (IN), U3.3 (EN)

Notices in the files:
ESPScreen-S3/ESPScreen-S3.kicad_pcb:
©️ 2024 zeankun.dev.
logo ©️ choco panda kat
all rights reserved
© 2024
LCDRucksack/LCDRucksack.kicad_pcb:
(c) 2024 zeankun.dev
